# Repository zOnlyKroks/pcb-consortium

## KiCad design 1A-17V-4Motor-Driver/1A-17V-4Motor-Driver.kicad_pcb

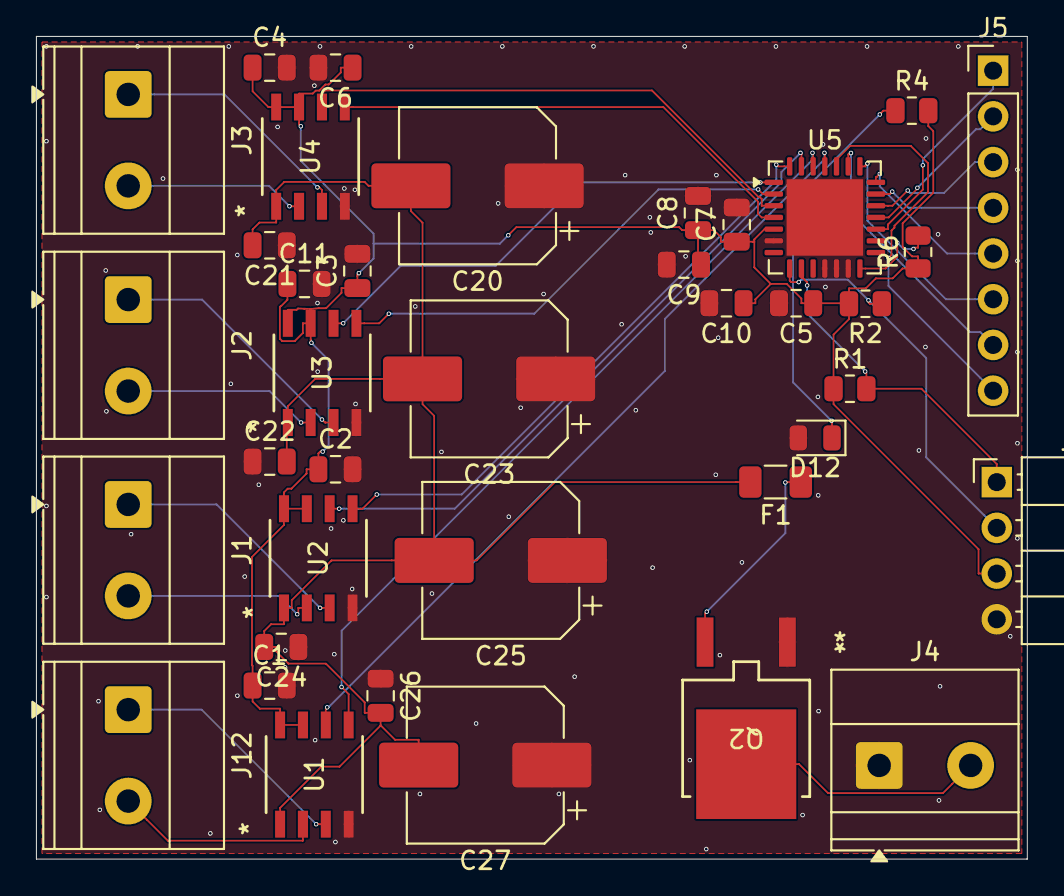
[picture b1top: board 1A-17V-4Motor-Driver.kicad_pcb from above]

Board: 2 copper layers, 55.1 x 45.7 mm, 38 parts (0 on the bottom side), 33 nets.

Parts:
C1, C2, C3, C4, C5, C21, C22, C24, C26: 0.1 uF; C_0805_2012Metric
C6, C7, C8, C9, C10, C11: 22 uF; C_0805_2012Metric
C20, C23, C25, C27: 220 uF; CP_Elec_8x10.5
D12: LED; LED_0805_2012Metric
F1: 4A Fuse; Fuse_1206_3216Metric
J1: OUT2; TerminalBlock_Phoenix_MKDS-1,5-2-5.08_1x02_P5.08mm_Horizont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
J2: OUT3; TerminalBlock_Phoenix_MKDS-1,5-2-5.08_1x02_P5.08mm_Horizont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
J3: OUT4; TerminalBlock_Phoenix_MKDS-1,5-2-5.08_1x02_P5.08mm_Horizont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
J4: 18V; TerminalBlock_Phoenix_MKDS-1,5-2-5.08_1x02_P5.08mm_Horizont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
J5: MUX; PinHeader_1x08_P2.54mm_Vertical
J6: Conn_01x04_Pin; PinHeader_1x04_P2.54mm_Horizontal
J12: OUT1; TerminalBlock_Phoenix_MKDS-1,5-2-5.08_1x02_P5.08mm_Horizont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
Q2: AOD4185; TO252_AOS
R1, R2: 4.7k; R_0805_2012Metric
R4: 330; R_0805_2012Metric
R6: 10k; R_0805_2012Metric
U1, U2, U3, U4: TPM8837C-SO1R; SOP-8_TPK
U5: MCP23017_ML; QFN-28-1EP_6x6mm_P0.65mm_EP4.25x4.25mm

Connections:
+VDC: C20.2, C21.2, C22.2, C23.2, C24.2, C25.2, C26.2, C27.2, F1.2, U1.1 (VM), U2.1 (VM), U3.1 (VM), U4.1 (VM)
/IN1: U1.6 (IN1), U5.25 (GPB0)
/IN2: U1.5 (IN2), U5.26 (GPB1)
/IN3: U2.6 (IN1), U5.27 (GPB2)
/IN4: U2.5 (IN2), U5.28 (GPB3)
/IN5: U3.6 (IN1), U5.1 (GPB4)
/IN6: U3.5 (IN2), U5.2 (GPB5)
/IN7: U4.6 (IN1), U5.3 (GPB6)
/IN8: U4.5 (IN2), U5.4 (GPB7)
/SCK: J6.2, R2.1, U5.8 (SCK)
/SDA: J6.1, R1.2, U5.9 (SDA)
GND: C1.2, C2.2, C3.2, C4.2, C5.2, C6.2, C7.2, C8.2, C9.2, C10.2, C11.2, C20.1, C21.1, C22.1, C23.1, C24.1, C25.1, C26.1, C27.1, D12.2 (A), J4.1, J6.4, Q2.1 (G), U1.4 (GND), U2.4 (GND), U3.4 (GND), U4.4 (GND), U5.6 (VSS), U5.11 (A0), U5.12 (A1), U5.13 (A2), U5.29 (EP)
unnamed: D12.1 (K), R4.1
unnamed: J1.1, U2.3 (OUT2)
unnamed: J1.2, U2.2 (OUT1)
unnamed: J2.1, U3.3 (OUT2)
unnamed: J2.2, U3.2 (OUT1)
unnamed: J3.1, U4.3 (OUT2)
unnamed: J3.2, U4.2 (OUT1)
unnamed: J4.2, Q2.2 (D)
unnamed: J5.1, U5.17 (GPA0)
unnamed: J5.2, U5.18 (GPA1)
unnamed: J5.3, U5.19 (GPA2)
unnamed: J5.4, U5.20 (GPA3)
unnamed: J5.5, U5.21 (GPA4)
unnamed: J5.6, U5.22 (GPA5)
unnamed: J5.7, U5.23 (GPA6)
unnamed: J5.8, U5.24 (GPA7)
unnamed: J12.1, U1.3 (OUT2)
unnamed: J12.2, U1.2 (OUT1)
unnamed: F1.1, Q2.3 (S)
unnamed: R6.2, U5.14 (~RESET)
VCC: C1.1, C2.1, C3.1, C4.1, C5.1, C6.1, C7.1, C8.1, C9.1, C10.1, C11.1, J6.3, R1.1, R2.2, R4.2, R6.1, U1.7 (NSLEEP), U1.8 (VCC), U2.7 (NSLEEP), U2.8 (VCC), U3.7 (NSLEEP), U3.8 (VCC), U4.7 (NSLEEP), U4.8 (VCC), U5.5 (VDD)

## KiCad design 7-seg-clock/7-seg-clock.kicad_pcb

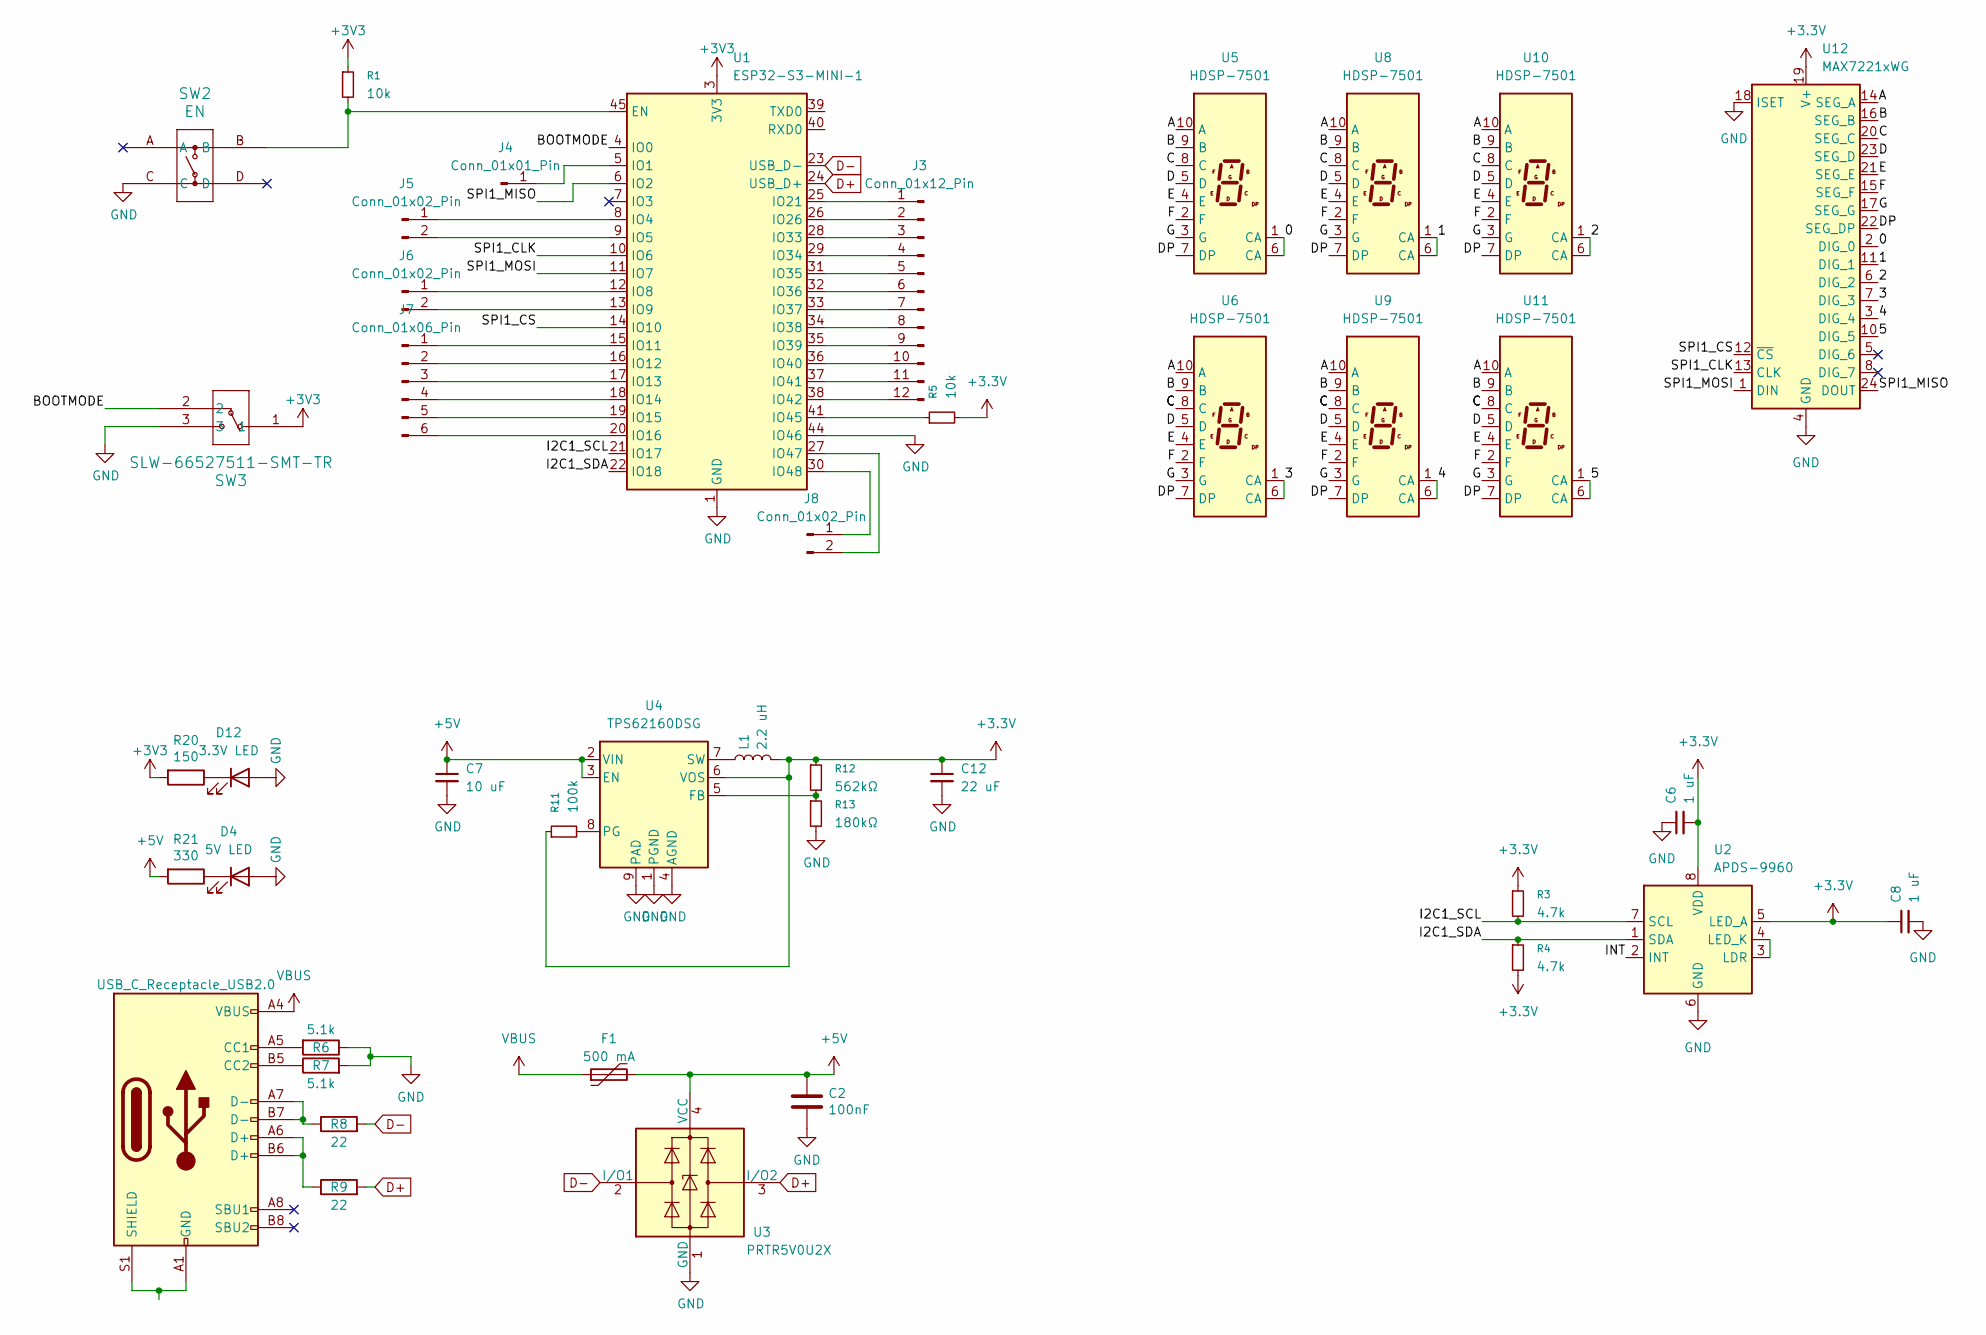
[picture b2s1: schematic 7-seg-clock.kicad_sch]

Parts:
C2: 100nF; C_0805_2012Metric; LCSC C28233
C6, C8: 1 uF; C_1206_3216Metric
C7: 10 uF; C_0805_2012Metric; LCSC Part # C15850
C12: 22 uF; C_0805_2012Metric; LCSC Part # C45783
D4: 5V LED; LED_0805_2012Metric; LCSC Part # C98225
D12: 3.3V LED; LED_0805_2012Metric; LCSC Part # C98225
F1: 500 mA; Fuse_1206_3216Metric; LCSC C135341
J1: USB_C_Receptacle_USB2.0; USB_C_Receptacle_HRO_TYPE-C-31-M-12; JlcRotOffset 180
J3: Conn_01x12_Pin; PinHeader_1x12_P2.54mm_Vertical
J4: Conn_01x01_Pin; PinHeader_1x01_P2.54mm_Vertical
J5, J6, J8: Conn_01x02_Pin; PinHeader_1x02_P2.54mm_Vertical; LCSC Part # C42431798
J7: Conn_01x06_Pin; PinHeader_1x06_P2.54mm_Vertical
L1: 2.2 uH; IND_PA4332.222NLT; LCSC Part # C3222957
R1, R5: 10k; R_0805_2012Metric; LCSC Part # C17414
R3, R4: 4.7k; R_1206_3216Metric
R6, R7: 5.1k; R_0805_2012Metric; LCSC Part # C27834
R8, R9: 22; R_0805_2012Metric; LCSC Part # C17561
R11: 100k; R_0805_2012Metric; LCSC Part # C149504
R12: 562kΩ; R_0805_2012Metric; LCSC Part # C2849274
R13: 180kΩ; R_0805_2012Metric; LCSC Part # C17501
R20: 150; R_0805_2012Metric; LCSC Part # C17471
R21: 330; R_0805_2012Metric; LCSC Part # C17630
SW2: EN; KH-6X6X5H-STM_SKE; LCSC Part # C2837531
SW3: SLW-66527511-SMT-TR; SLW-66527511-SMT-TR_CUD
U1: ESP32-S3-MINI-1; ESP32-S2-MINI-1; LCSC Part # C2913206
U2: APDS-9960; Avago_APDS-9960
U3: PRTR5V0U2X; SOT-143; LCSC C2827688
U4: TPS62160DSG; WSON-8-1EP_2x2mm_P0.5mm_EP0.9x1.6mm_ThermalVias; LCSC Part # C324077
U5, U6, U8, U9, U10, U11: HDSP-7501; HDSP-A151
U12: MAX7221xWG; SOIC-24W_7.5x15.4mm_P1.27mm

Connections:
+3.3V: C6.2, C8.1, C12.1, L1.2, R3.1, R4.2, R5.2, R11.1, R12.1, U2.5 (LED_A), U2.8 (VDD), U4.6 (VOS), U12.19 (V+)
+3V3: R1.1, R20.2, SW3.1, U1.3 (3V3)
+5V: C2.1, C7.1, F1.2, R21.2, U3.4 (VCC), U4.2 (VIN), U4.3 (EN)
/0: U5.1 (CA), U5.6 (CA), U12.2 (DIG_0)
/1: U8.1 (CA), U8.6 (CA), U12.11 (DIG_1)
/2: U10.1 (CA), U10.6 (CA), U12.6 (DIG_2)
/3: U6.1 (CA), U6.6 (CA), U12.7 (DIG_3)
/4: U9.1 (CA), U9.6 (CA), U12.3 (DIG_4)
/5: U11.1 (CA), U11.6 (CA), U12.10 (DIG_5)
/A: U5.10 (A), U6.10 (A), U8.10 (A), U9.10 (A), U10.10 (A), U11.10 (A), U12.14 (SEG_A)
/B: U5.9 (B), U6.9 (B), U8.9 (B), U9.9 (B), U10.9 (B), U11.9 (B), U12.16 (SEG_B)
/BOOTMODE: SW3.2, U1.4 (IO0)
/C: U5.8 (C), U6.8 (C), U8.8 (C), U9.8 (C), U10.8 (C), U11.8 (C), U12.20 (SEG_C)
/D: U5.5 (D), U6.5 (D), U8.5 (D), U9.5 (D), U10.5 (D), U11.5 (D), U12.23 (SEG_D)
/DP: U5.7 (DP), U6.7 (DP), U8.7 (DP), U9.7 (DP), U10.7 (DP), U11.7 (DP), U12.22 (SEG_DP)
/E: U5.4 (E), U6.4 (E), U8.4 (E), U9.4 (E), U10.4 (E), U11.4 (E), U12.21 (SEG_E)
/F: U5.2 (F), U6.2 (F), U8.2 (F), U9.2 (F), U10.2 (F), U11.2 (F), U12.15 (SEG_F)
/G: U5.3 (G), U6.3 (G), U8.3 (G), U9.3 (G), U10.3 (G), U11.3 (G), U12.17 (SEG_G)
/I2C1_SCL: R3.2, U1.21 (IO17), U2.7 (SCL)
/I2C1_SDA: R4.1, U1.22 (IO18), U2.1 (SDA)
/INT: U2.2 (INT)
/SPI1_CLK: U1.10 (IO6), U12.13 (CLK)
/SPI1_CS: U1.14 (IO10), U12.12 (~CS)
/SPI1_MISO: U1.6 (IO2), U12.24 (DOUT)
/SPI1_MOSI: U1.11 (IO7), U12.1 (DIN)
D+: R9.2, U1.24 (USB_D+), U3.3 (I/O2)
D-: R8.2, U1.23 (USB_D-), U3.2 (I/O1)
GND: C2.2, C6.1, C7.2, C8.2, C12.2, D4.2 (A), D12.2 (A), R6.1, R7.2, R13.2, SW2.C, SW3.3, U1.1 (GND), U1.2 (GND), U1.42 (GND), U1.43 (GND), U1.44 (IO46), U1.46 (GND), U1.47 (GND), U1.48 (GND), U1.49 (GND), U1.50 (GND), U1.51 (GND), U1.52 (GND), U1.53 (GND), U1.54 (GND), U1.55 (GND), U1.56 (GND), U1.57 (GND), U1.58 (GND), U1.59 (GND), U1.60 (GND), U1.61 (GND), U1.62 (GND), U1.63 (GND), U1.64 (GND), U1.65 (GND), U2.6 (GND), U3.1 (GND), U4.1 (PGND), U4.4 (AGND), U4.9 (PAD), U12.4 (GND), U12.9 (GND), U12.18 (ISET)
unnamed: D4.1 (K), R21.1
unnamed: D12.1 (K), R20.1
unnamed: J1.A5 (CC1), R6.2
unnamed: J1.B5 (CC2), R7.1
unnamed: J1.A6 (D+), J1.B6 (D+), R9.1
unnamed: J1.A7 (D-), J1.B7 (D-), R8.1
unnamed: J1.A1 (GND), J1.A12 (GND), J1.B1 (GND), J1.B12 (GND), J1.S1 (SHIELD)
unnamed: J3.1, U1.25 (IO21)
unnamed: J3.2, U1.26 (IO26)
unnamed: J3.3, U1.28 (IO33)
unnamed: J3.4, U1.29 (IO34)
unnamed: J3.5, U1.31 (IO35)
unnamed: J3.6, U1.32 (IO36)
unnamed: J3.7, U1.33 (IO37)
unnamed: J3.8, U1.34 (IO38)
unnamed: J3.9, U1.35 (IO39)
unnamed: J3.10, U1.36 (IO40)
unnamed: J3.11, U1.37 (IO41)
unnamed: J3.12, U1.38 (IO42)
unnamed: J4.1, U1.5 (IO1)
unnamed: J5.1, U1.8 (IO4)
unnamed: J5.2, U1.9 (IO5)
unnamed: J6.1, U1.12 (IO8)
unnamed: J6.2, U1.13 (IO9)
unnamed: J7.1, U1.15 (IO11)
unnamed: J7.2, U1.16 (IO12)
unnamed: J7.3, U1.17 (IO13)
unnamed: J7.4, U1.18 (IO14)
unnamed: J7.5, U1.19 (IO15)
unnamed: J7.6, U1.20 (IO16)
unnamed: J8.1, U1.30 (IO48)
unnamed: J8.2, U1.27 (IO47)
unnamed: R1.2, SW2.B, U1.45 (EN)
unnamed: R5.1, U1.41 (IO45)
unnamed: U2.3 (LDR), U2.4 (LED_K)
unnamed: R12.2, R13.1, U4.5 (FB)
unnamed: R11.2, U4.8 (PG)
unnamed: L1.1, U4.7 (SW)
VBUS: F1.1, J1.A4 (VBUS), J1.A9 (VBUS), J1.B4 (VBUS), J1.B9 (VBUS)

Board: 6 copper layers, 42 parts (0 on the bottom side), 66 nets, no tracks yet.

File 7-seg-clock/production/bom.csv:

Designator,Footprint,Quantity,Value,LCSC Part #
C12,0805,1,22 uF,C45783
C2,0805,1,100nF,C28233
"C6, C8",1206,2,1 uF,
C7,0805,1,10 uF,C15850
D12,0805,1,3.3V LED,C98225
D4,0805,1,5V LED,C98225
F1,1206,1,500 mA,C135341
J1,USB_C_Receptacle_HRO_TYPE-C-31-M-12,1,USB_C_Receptacle_USB2.0,C165948
J3,PinHeader_1x12_P2.54mm_Vertical,1,Conn_01x12_Pin,
J4,PinHeader_1x01_P2.54mm_Vertical,1,Conn_01x01_Pin,
"J5, J6, J8",PinHeader_1x02_P2.54mm_Vertical,3,Conn_01x02_Pin,C42431798
J7,PinHeader_1x06_P2.54mm_Vertical,1,Conn_01x06_Pin,
L1,IND_PA4332.222NLT,1,2.2 uH,C3222957
"R1, R5",0805,2,10k,C17414
R11,0805,1,100k,C149504
R12,0805,1,562kΩ,C2849274
R13,0805,1,180kΩ,C17501
R20,0805,1,150,C17471
R21,0805,1,330,C17630
"R3, R4",1206,2,4.7k,
"R6, R7",0805,2,5.1k,C27834
"R8, R9",0805,2,22,C17561
SW2,KH-6X6X5H-STM_SKE,1,EN,C2837531 
SW3,SLW-66527511-SMT-TR_CUD,1,SLW-66527511-SMT-TR,
U1,ESP32-S2-MINI-1,1,ESP32-S3-MINI-1,C2913206 
"U10, U11, U5, U6, U8, U9",HDSP-A151,6,HDSP-7501,
U12,SOIC-24W_7.5x15.4mm_P1.27mm,1,MAX7221xWG,
U2,Avago_APDS-9960,1,APDS-9960,
U3,SOT-143,1,PRTR5V0U2X,C2827688
U4,WSON-8-1EP_2x2mm_P0.5mm_EP0.9x1.6mm_ThermalVias,1,TPS62160DSG,C324077

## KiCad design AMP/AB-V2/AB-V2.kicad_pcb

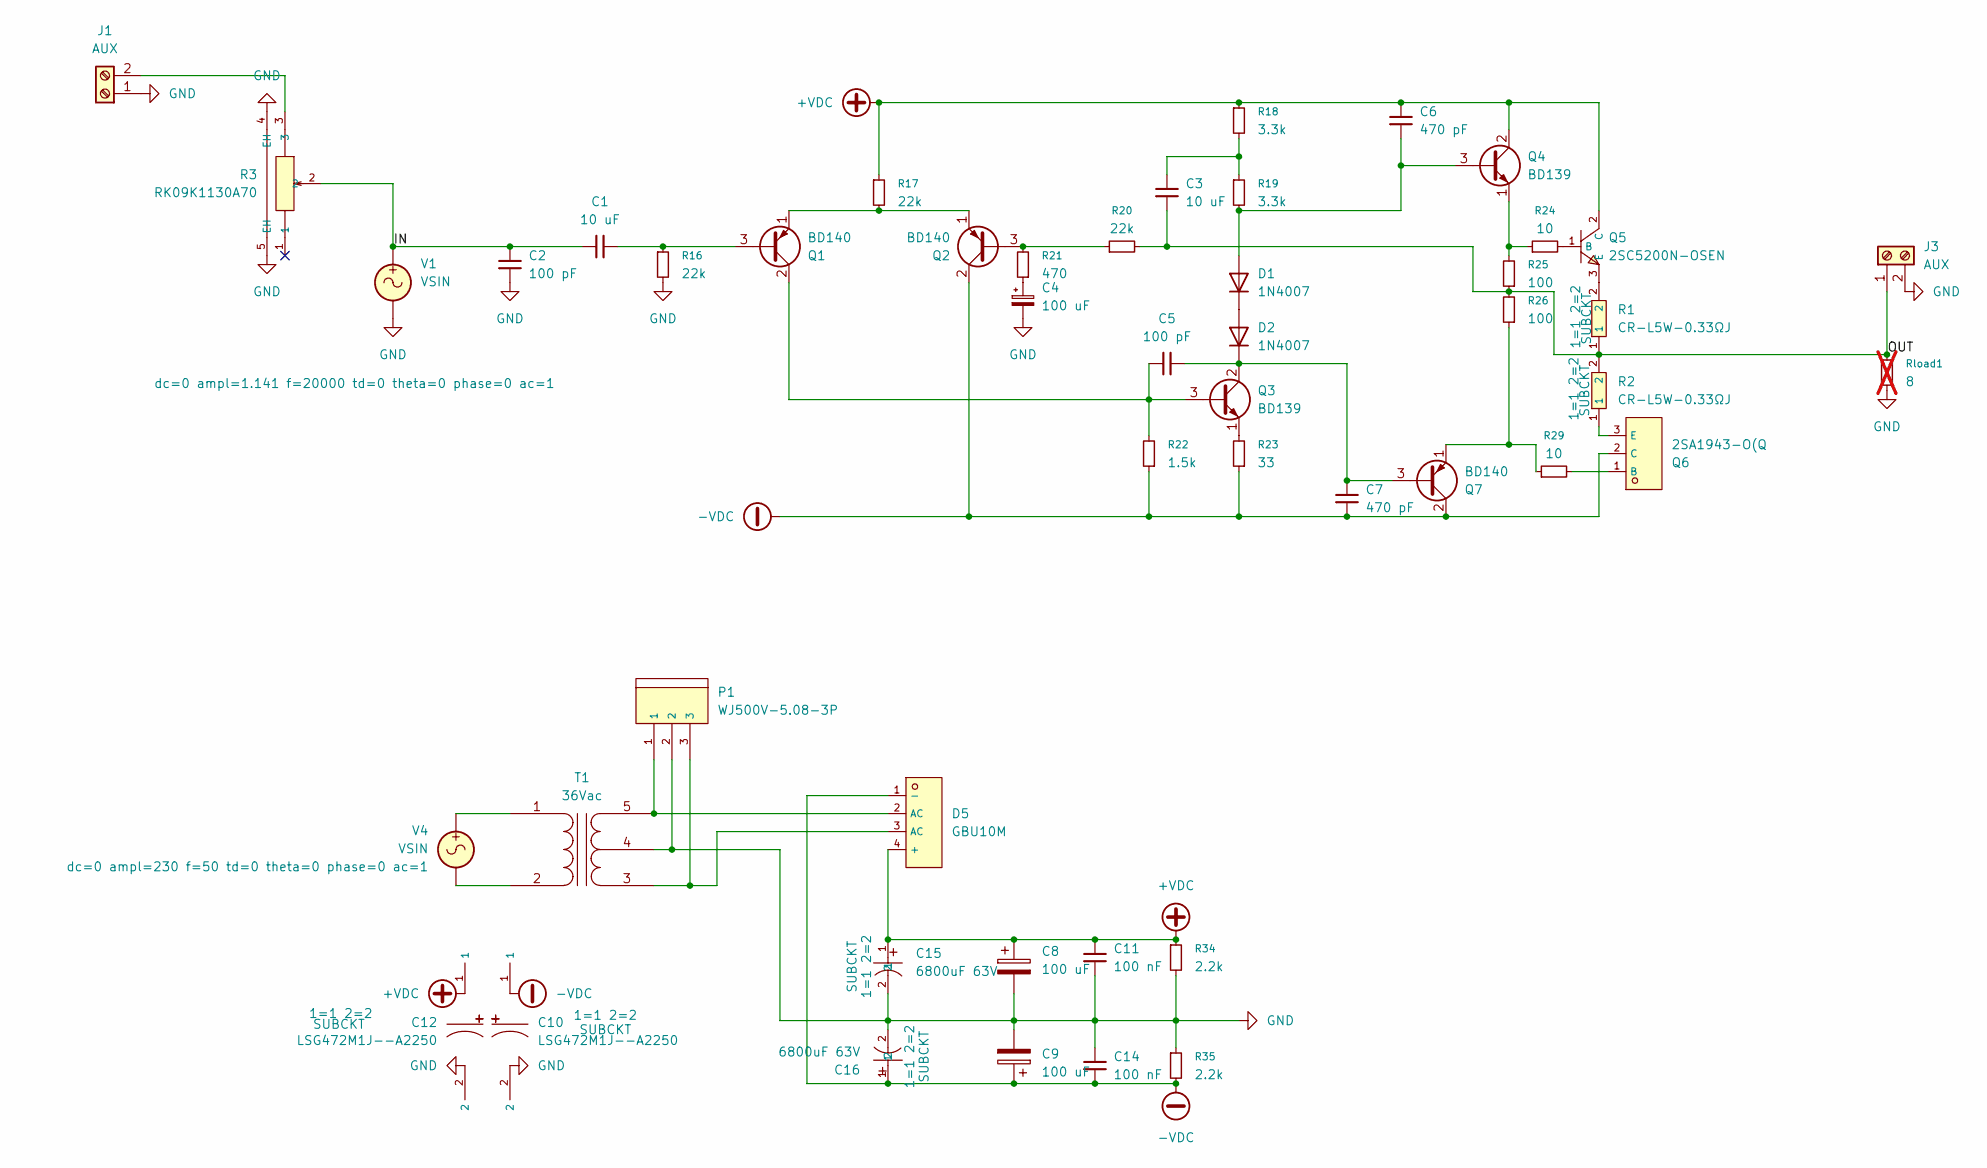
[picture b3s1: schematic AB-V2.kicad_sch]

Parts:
C1, C3: 10 uF; C_1206_3216Metric
C2, C5: 100 pF; C_1206_3216Metric
C4: 100 uF; C_Elec_6.3x7.7
C6, C7: 470 pF; C_1206_3216Metric
C8, C9: 100 uF; CP_Radial_D8.0mm_P3.50mm
C10, C12: LSG472M1J--A2250; C316462_CAP-TH_BD22_0-P10_00-D2_3-FD; LCSC C316462
C11, C14: 100 nF; C_0805_2012Metric
C15, C16: 6800uF 63V; C46441_CAP-TH_BD25_0-P10_00-D2_3-FD; LCSC C46441
D1, D2: 1N4007; D_DO-41_SOD81_P10.16mm_Horizontal
D5: GBU10M; C970322_GBU_4P-L22_0-W3_5-P5_08; LCSC C970322
J1, J3: AUX; WJ500V-5.08-2P
P1: WJ500V-5.08-3P; C72334_CONN-TH_3P-P5_00_WJ500V-5_08-3P; LCSC C72334
Q1, Q2, Q7: BD140; TO-126-3_Vertical
Q3, Q4: BD139; TO-126-3_Vertical
Q5: 2SC5200N-OSEN; C49055716_TO-3P-3_L15_6-W4_8-P5_45-L; LCSC C49055716
Q6: 2SA1943-O(Q; C545244_TO-3PL_L20_0-W5_0-P5_45-L_1; LCSC C545244
R1, R2: CR-L5W-0.33ΩJ; C334290_RES-TH_BD9_5-L22_0-P26_00-D0_7; LCSC C334290
R3: RK09K1130A70; C351173_RES-TH_RK09K1130A70; LCSC C351173
R16, R17, R20: 22k; R_0805_2012Metric
R18, R19: 3.3k; R_0805_2012Metric
R21: 470; R_0805_2012Metric
R22: 1.5k; R_0805_2012Metric
R23: 33; R_0805_2012Metric
R24, R29: 10; R_0805_2012Metric
R25, R26: 100; R_1206_3216Metric
R34, R35: 2.2k; R_0805_2012Metric
Rload1: 8; not fitted
T1: 36Vac
V1, V4: VSIN; TQFP-44_10x10mm_P0.8mm

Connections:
+VDC: C6.2, C8.1, C11.2, C12.1, C15.1, D5.4 (+), Q4.2 (C), Q5.2 (C), R17.1, R18.1, R34.1
-VDC: C7.1, C9.1, C10.1, C14.1, C16.1, D5.1 (-), Q2.2 (C), Q6.2 (C), Q7.2 (C), R22.1, R23.1, R35.2
/IN: C1.1, C2.2, R3.2, V1.1
/OUT: C3.1, J3.1, R1.1, R2.2, R20.2, R25.1, R26.2, Rload1.2
GND: C2.1, C4.2, C8.2, C9.2, C10.2, C11.1, C12.2, C14.2, C15.2, C16.2, J1.1, J3.2, P1.2, R3.4 (EH), R3.5 (EH), R16.2, R34.2, R35.1, Rload1.1, T1.4 (SC), V1.2
unnamed: C3.2, R18.2, R19.1
unnamed: C4.1, R21.1
unnamed: C6.1, D1.2 (A), Q4.3 (B), R19.2
unnamed: D1.1 (K), D2.2 (A)
unnamed: C5.1, C7.2, D2.1 (K), Q3.2 (C), Q7.3 (B)
unnamed: D5.2 (AC), P1.1, T1.5 (SB)
unnamed: D5.3 (AC), P1.3, T1.3 (SA)
unnamed: J1.2, R3.3
unnamed: C1.2, Q1.3 (B), R16.1
unnamed: C5.2, Q1.2 (C), Q3.3 (B), R22.2
unnamed: Q1.1 (E), Q2.1 (E), R17.2
unnamed: Q2.3 (B), R20.1, R21.2
unnamed: Q3.1 (E), R23.2
unnamed: Q4.1 (E), R24.1, R25.2
unnamed: Q5.1 (B), R24.2
unnamed: Q5.3 (E), R1.2
unnamed: Q6.1 (B), R29.2
unnamed: Q6.3 (E), R2.1
unnamed: Q7.1 (E), R26.1, R29.1
unnamed: T1.1 (AA), V4.1
unnamed: T1.2 (AB), V4.2

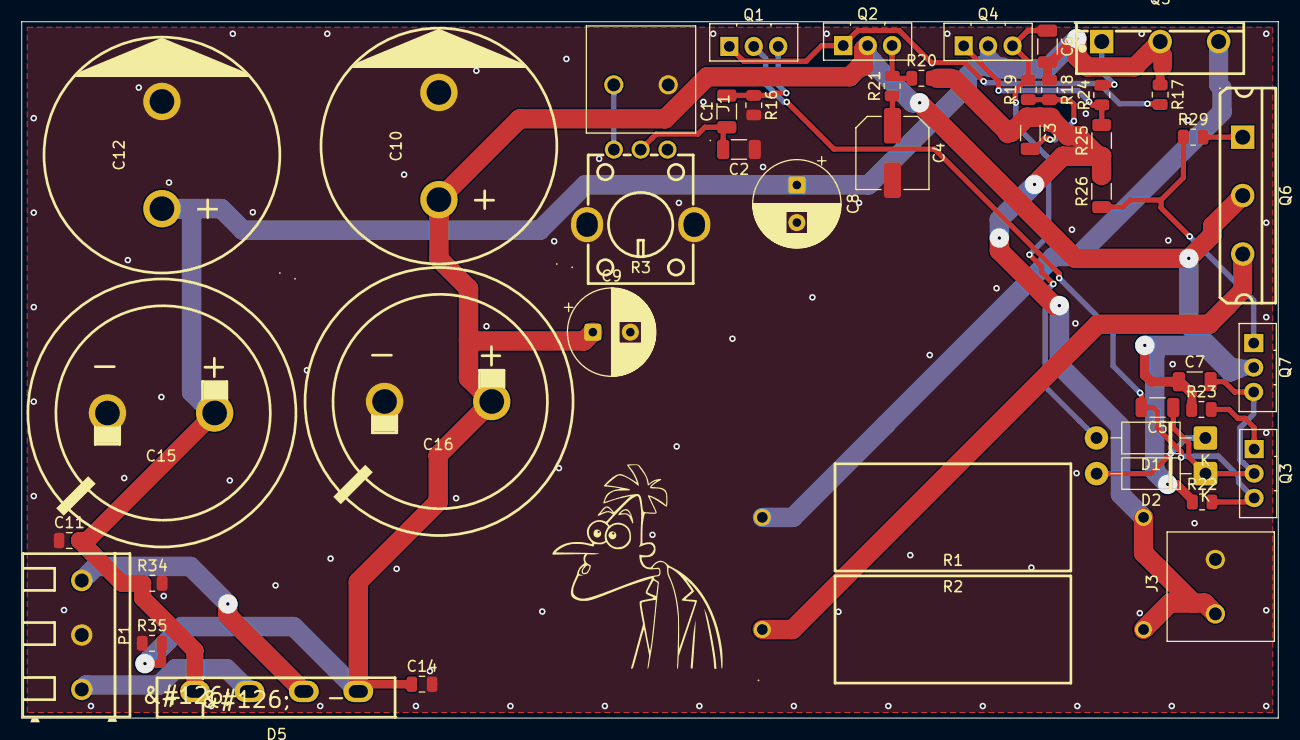
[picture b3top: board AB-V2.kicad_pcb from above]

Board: 2 copper layers, 117.2 x 65.0 mm, 45 parts (0 on the bottom side), 24 nets.

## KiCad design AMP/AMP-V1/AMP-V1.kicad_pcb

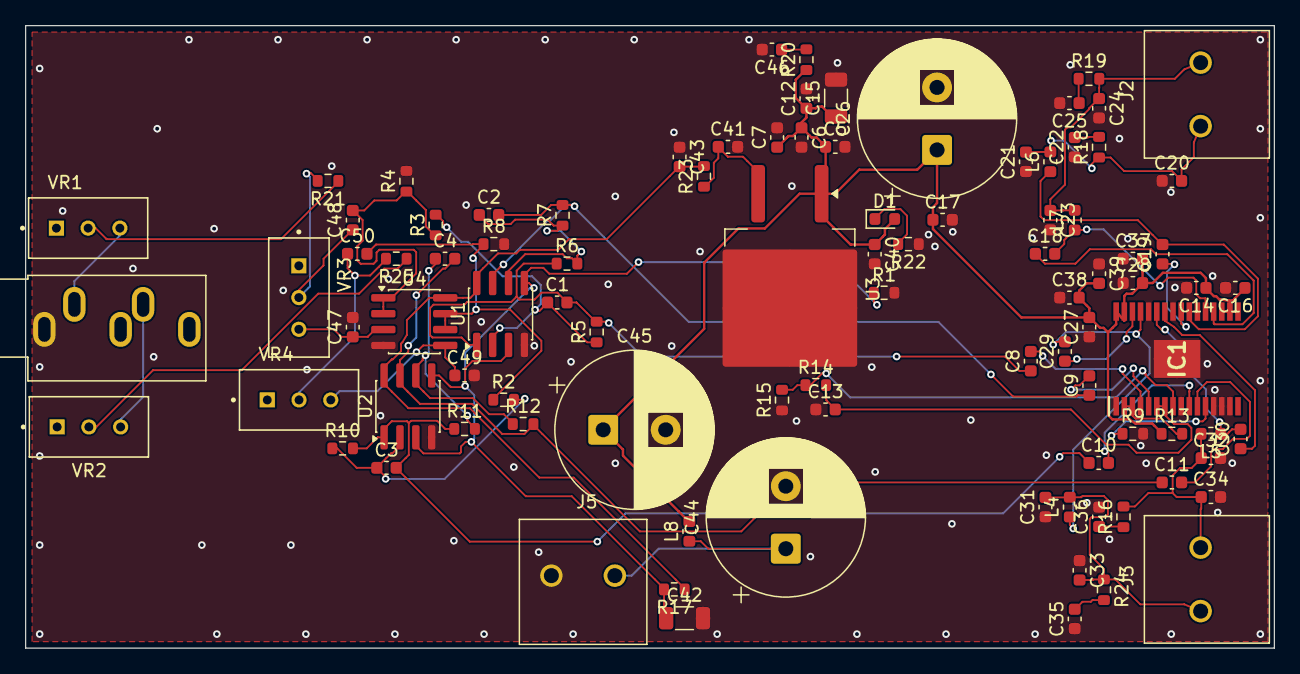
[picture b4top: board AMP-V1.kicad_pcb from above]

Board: 2 copper layers, 99.9 x 49.8 mm, 94 parts (0 on the bottom side), 50 nets.

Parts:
C1, C2, C3, C4: 22 pF; C_0603_1608Metric
C5, C8, C9, C10, C11, C16, C27, C28, C38, C40, C41: 10uF; C_0603_1608Metric
C6, C7, C12, C17, C39, C46: 100nF; C_0603_1608Metric
C13: 2.2 uF; C_0603_1608Metric
C14, C37, C43: 220 uF; C_0603_1608Metric
C15, C42: 47uF; C_1206_3216Metric
C18, C19, C29, C30: 0.22 uF; C_0603_1608Metric
C20, C23, C31, C32: 680 nF; C_0603_1608Metric
C21, C24, C33, C34: 1 nF; C_0603_1608Metric
C22, C25, C35, C36, C47, C48, C49, C50: 10 nF; C_0603_1608Metric
C26, C44, C45: 470 uF; CP_Radial_D12.5mm_P5.00mm
D1: LED; LED_0603_1608Metric
IC1: TPA3116D2DAD; SOP65P810X120-33N
J2: L; WJ500V-5.08-2P
J3, J5: R; WJ500V-5.08-2P
J4: AudioJack3_SwitchTR; Jack_3.5mm_CUI_SJ1-3535NG_Horizontal
L4, L5, L6, L7, L8: 10 uH; L_0603_1608Metric
R1, R2, R3, R5, R6, R7, R10, R11, R12, R17, R21, R22, R25: 10K; R_0603_1608Metric
R4, R8, R9, R13: 100K; R_0603_1608Metric
R14: 75k Ohm; R_0603_1608Metric
R15: 47k Ohm; R_0603_1608Metric
R16, R18, R19, R20, R24: 3.3 Ohm; R_0603_1608Metric
R23: 2.2 Ohm; R_0603_1608Metric
U1, U2, U4: NE5532; SOIC-8_3.9x4.9mm_P1.27mm
U3: LM7812_TO220; TO-263-2
VR1, VR2, VR3, VR4: 3296W-1-103LF; TRIM_3296W-1-103LF

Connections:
+12V: C43.2, R17.1, R23.2, U1.8 (V+), U2.8 (V+), U4.8 (V+)
/GAIN: IC1.8 (GAIN/SLV), R14.1, R15.2
/GVDD: C13.2, IC1.6 (PLIMIT), IC1.7 (GVDD), R14.2
/LIN-N: C4.2, C11.1, R12.2, U2.7
/LIN-P: C3.2, C10.1, R10.2, R11.1, U2.1
/LR-Decode/MID-REF: C42.1, R1.1, R17.2, U1.3 (+), U1.5 (+), U2.3 (+), U2.5 (+)
/RIN-N: C2.2, C9.1, R7.2, U1.7
/RIN-P: C1.2, C8.1, R5.2, R6.1, U1.1
/RING-RIGHT: R25.1, VR2.2
/TIP-LEFT: R21.1, VR1.2
GND: C5.2, C6.2, C7.2, C12.2, C13.1, C14.2, C15.2, C16.2, C17.2, C20.1, C21.1, C22.1, C23.2, C24.2, C25.2, C26.2, C27.1, C28.1, C31.1, C32.2, C33.1, C34.2, C35.1, C36.2, C37.1, C38.1, C39.1, C40.2, C41.2, C42.2, C43.1, C44.2, C45.2, C46.2, C47.2, C49.2, IC1.1 (MODSEL), IC1.9 (GND_1), IC1.13 (AM2), IC1.14 (AM1), IC1.15 (AM0), IC1.25 (GND_3), IC1.28 (GND_4), IC1.33 (GND_5), J4.S, J5.1, R1.2, R4.2, R8.2, R9.2, R15.1, R22.1, U1.4 (V-), U2.4 (V-), U3.2 (GND), U4.4 (V-)
unnamed: C22.2, R18.2
unnamed: C25.1, R19.1
unnamed: C35.2, R24.2
unnamed: C36.1, R16.1
unnamed: C46.1, R20.2
unnamed: C48.1, R21.2, VR3.2
unnamed: C50.1, R25.2, VR4.2
unnamed: D1.1 (K), R22.2
unnamed: C18.1, IC1.20 (BSNL)
unnamed: C30.1, IC1.26 (BSNR)
unnamed: C19.1, IC1.24 (BSPL)
unnamed: C29.1, IC1.30 (BSPR)
unnamed: IC1.2 (SD), IC1.3 (FAULT), R13.2
unnamed: C11.2, IC1.11 (LINN)
unnamed: C10.2, IC1.10 (LINP)
unnamed: IC1.12 (MUTE), R9.1
unnamed: C18.2, IC1.21 (OUTNL), L7.1
unnamed: C30.2, IC1.27 (OUTNR), L5.1
unnamed: C19.2, IC1.23 (OUTPL), L6.1
unnamed: C29.2, IC1.29 (OUTPR), L4.1
unnamed: C9.2, IC1.5 (RINN)
unnamed: C8.2, IC1.4 (RINP)
unnamed: C20.2, C21.2, J2.1, L6.2, R18.1
unnamed: C23.1, C24.1, J2.2, L7.2, R19.2
unnamed: C31.2, C33.2, J3.1, L4.2, R24.1
unnamed: C32.1, C34.1, J3.2, L5.2, R16.2
unnamed: J4.R, VR2.3
unnamed: J4.T, VR1.3
unnamed: C44.1, J5.2, L8.1
unnamed: C1.1, R3.2, R5.1, U1.2 (-)
unnamed: C2.1, R6.2, R7.1, U1.6 (-)
unnamed: C3.1, R2.2, R10.1, U2.2 (-)
unnamed: C4.1, R11.2, R12.1, U2.6 (-)
unnamed: C41.1, R23.1, U3.3 (VO)
unnamed: C47.1, U4.3 (+), VR3.3
unnamed: C48.2, R3.1, R4.1, U4.1, U4.2 (-)
unnamed: C49.1, U4.5 (+), VR4.3
unnamed: C50.2, R2.1, R8.1, U4.6 (-), U4.7
PVCC: C5.1, C6.1, C7.1, C12.1, C14.1, C15.1, C16.1, C17.1, C26.1, C27.2, C28.2, C37.2, C38.2, C39.2, C40.1, C45.1, D1.2 (A), IC1.17 (AVCC), IC1.18 (PVCC_1), IC1.19 (PVCC_2), IC1.31 (PVCC_3), IC1.32 (PVCC_4), L8.2, R13.1, R20.1, U3.1 (VI)

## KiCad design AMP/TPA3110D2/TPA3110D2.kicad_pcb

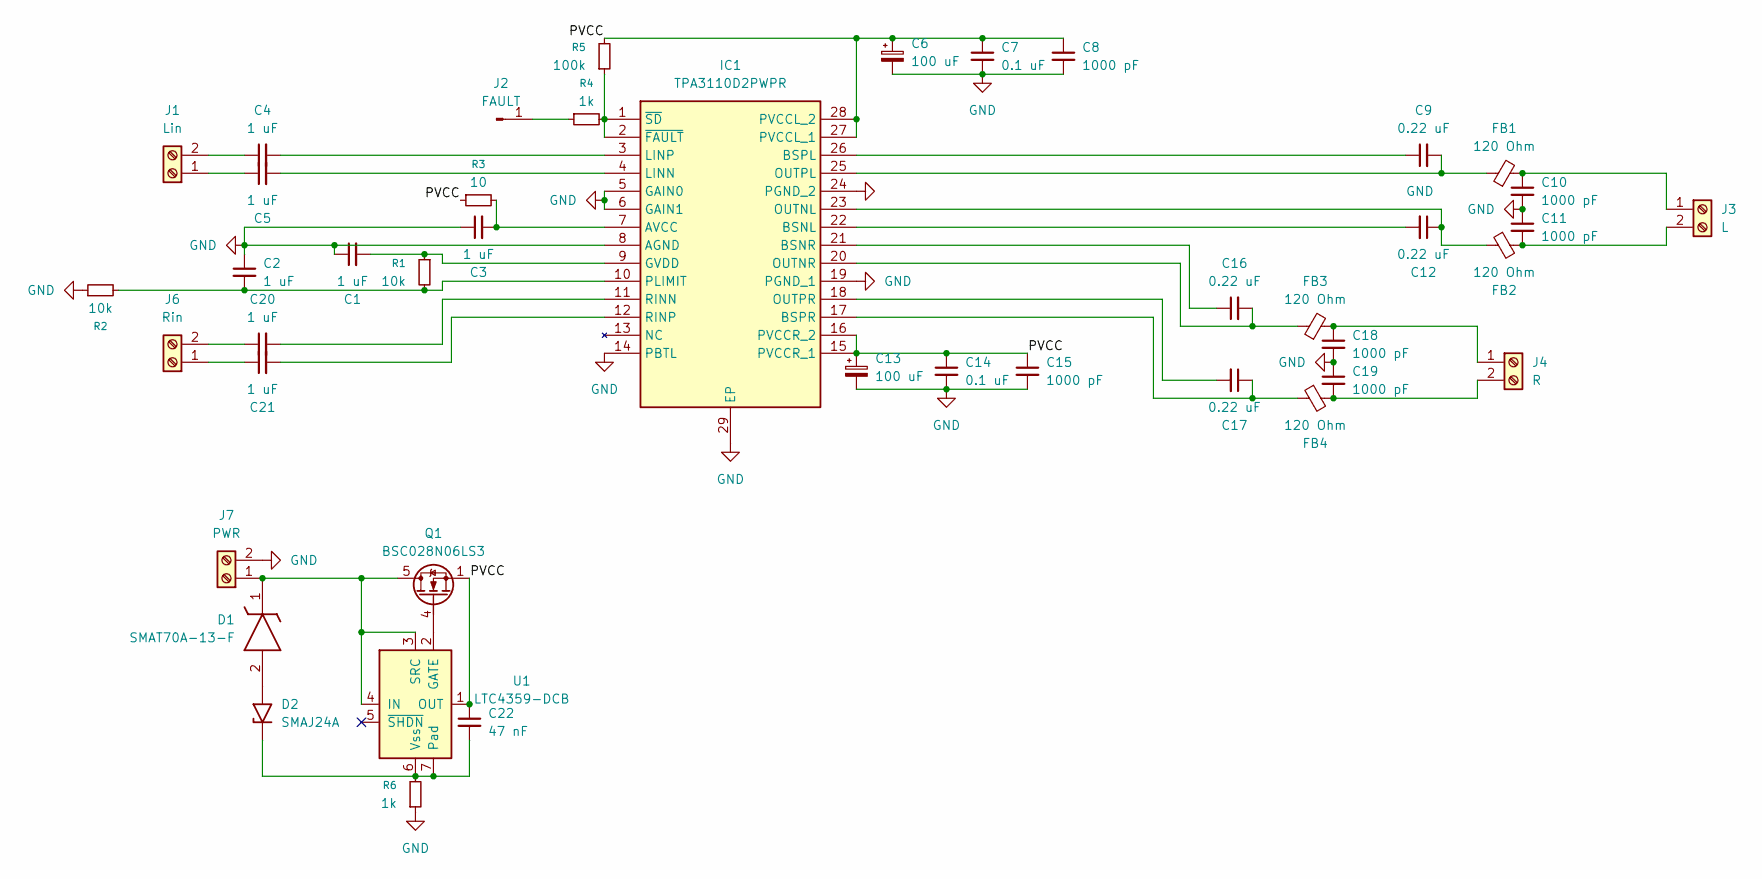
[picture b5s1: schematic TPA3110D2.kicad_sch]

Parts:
C1, C2, C3, C4, C5, C20, C21: 1 uF; C_0603_1608Metric
C6, C13: 100 uF; CP_Elec_6.3x7.7
C7, C14: 0.1 uF; C_0603_1608Metric
C8, C10, C11, C15, C18, C19: 1000 pF; C_0603_1608Metric
C9, C12, C16, C17: 0.22 uF; C_0603_1608Metric
C22: 47 nF; C_0603_1608Metric
D1: SMAT70A-13-F; DIOM5226X230N; Mouser Part Number 621-SMAT70A-13-F
D2: SMAJ24A; D_SMA
FB1, FB2, FB3, FB4: 120 Ohm; R_0603_1608Metric
IC1: TPA3110D2PWPR; SOP65P640X120-29N; Mouser Part Number 595-TPA3110D2PWPR
J1: Lin; WJ500V-5.08-2P
J2: FAULT; PinHeader_1x01_P2.54mm_Vertical
J3: L; WJ500V-5.08-2P
J4: R; WJ500V-5.08-2P
J6: Rin; WJ500V-5.08-2P
J7: PWR; WJ500V-5.08-2P
Q1: BSC028N06LS3; TDSON-8-1
R1, R2: 10k; R_0603_1608Metric
R3: 10; R_0603_1608Metric
R4, R6: 1k; R_0603_1608Metric
R5: 100k; R_0603_1608Metric
U1: LTC4359-DCB; DFN-6-1EP_3x2mm_P0.5mm_EP1.65x1.35mm

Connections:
/PVCC: C6.1, C7.1, C8.1, C13.1, C14.1, C15.1, C22.1, IC1.15 (PVCCR_1), IC1.16 (PVCCR_2), IC1.27 (PVCCL_1), IC1.28 (PVCCL_2), Q1.1 (S), Q1.2 (S), Q1.3 (S), R3.1, R5.2, U1.1 (OUT)
GND: C1.1, C2.1, C3.1, C6.2, C7.2, C8.2, C10.2, C11.1, C13.2, C14.2, C15.2, C18.2, C19.1, IC1.5 (GAIN0), IC1.6 (GAIN1), IC1.8 (AGND), IC1.14 (PBTL), IC1.19 (PGND_1), IC1.24 (PGND_2), IC1.29 (EP), J7.2, R2.1, R6.1
unnamed: D1.2 (A), D2.2 (A2)
unnamed: D1.1 (K), J7.1, Q1.5 (D), U1.3 (SRC), U1.4 (IN)
unnamed: C22.2, D2.1 (A1), R6.2, U1.6 (Vss), U1.7 (Pad)
unnamed: C3.2, IC1.7 (AVCC), R3.2
unnamed: C12.2, IC1.22 (BSNL)
unnamed: C16.1, IC1.21 (BSNR)
unnamed: C9.1, IC1.26 (BSPL)
unnamed: C17.1, FB4.1, IC1.17 (BSPR)
unnamed: C1.2, IC1.9 (GVDD), R1.1
unnamed: C5.2, IC1.4 (LINN)
unnamed: C4.2, IC1.3 (LINP)
unnamed: C12.1, FB2.1, IC1.23 (OUTNL)
unnamed: C16.2, FB3.1, IC1.20 (OUTNR)
unnamed: C9.2, FB1.1, IC1.25 (OUTPL)
unnamed: C17.2, IC1.18 (OUTPR)
unnamed: C2.2, IC1.10 (PLIMIT), R1.2, R2.2
unnamed: C20.2, IC1.11 (RINN)
unnamed: C21.2, IC1.12 (RINP)
unnamed: IC1.1 (~SD), IC1.2 (~FAULT), R4.2, R5.1
unnamed: C5.1, J1.1
unnamed: C4.1, J1.2
unnamed: J2.1 (Pin_1_1), R4.1
unnamed: C10.1, FB1.2, J3.1
unnamed: C11.2, FB2.2, J3.2
unnamed: C18.1, FB3.2, J4.1
unnamed: C19.2, FB4.2, J4.2
unnamed: C21.1, J6.1
unnamed: C20.1, J6.2
unnamed: Q1.4 (G), U1.2 (GATE)

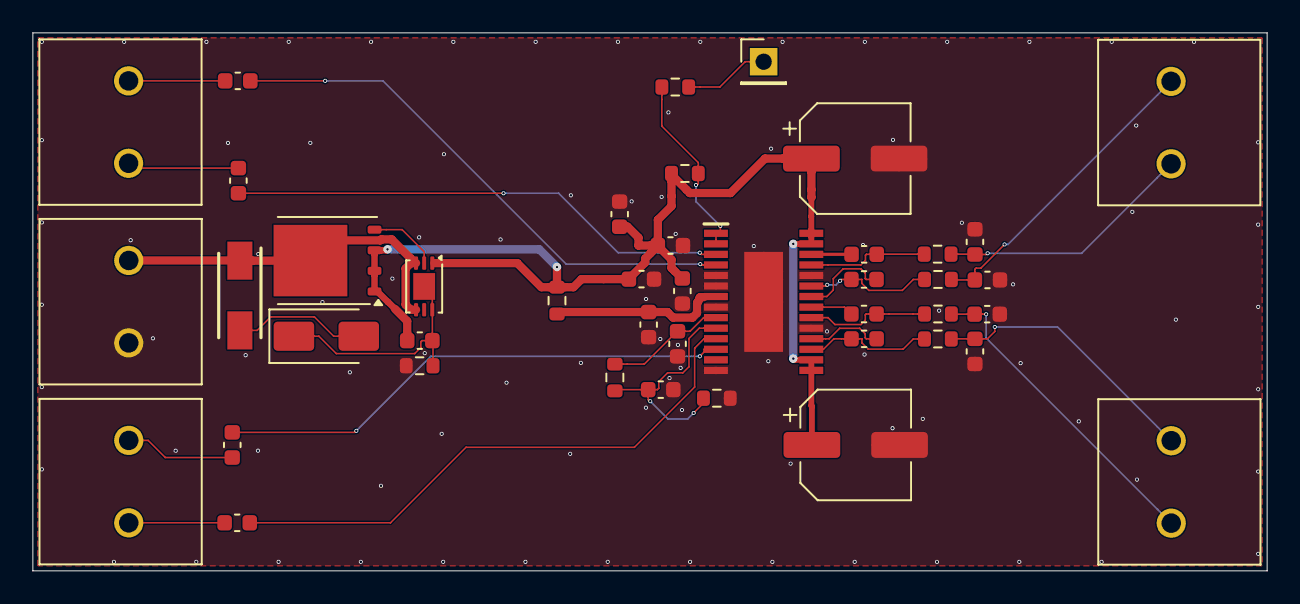
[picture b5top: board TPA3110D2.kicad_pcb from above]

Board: 2 copper layers, 76.1 x 33.2 mm, 43 parts (0 on the bottom side), 31 nets.

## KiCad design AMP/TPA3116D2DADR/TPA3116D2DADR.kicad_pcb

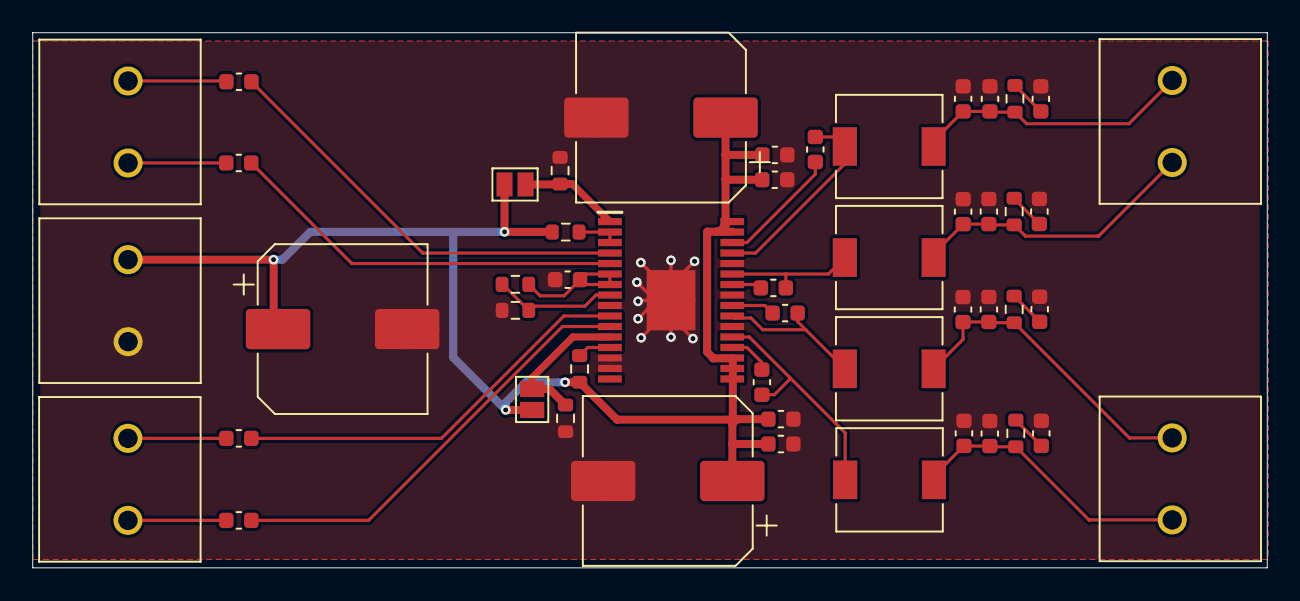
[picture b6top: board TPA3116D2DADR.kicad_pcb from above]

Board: 2 copper layers, 76.5 x 33.2 mm, 50 parts (0 on the bottom side), 32 nets.

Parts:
C1, C2, C3, C4, C5, C9, C12: 1 uF; C_0603_1608Metric
C8, C11, C14, C15, C16, C17: 100 nF; C_0603_1608Metric
C10, C13, C30: 220 uF; CP_Elec_10x10
C18, C19, C24, C25: 680 nF; C_0603_1608Metric
C20, C21, C26, C27: 1 nF; C_0603_1608Metric
C22, C23, C28, C29: 10 nF; C_0603_1608Metric
IC1: TPA3116D2DADR; SOP65P810X120-33N
J1: Rin; WJ500V-5.08-2P
J2: Lin; WJ500V-5.08-2P
J3: Rout; WJ500V-5.08-2P
J4: Lout; WJ500V-5.08-2P
J7: PWR; WJ500V-5.08-2P
JP1: mode_sel; SolderJumper-2_P1.3mm_Open_Pad1.0x1.5mm
JP2: mute; SolderJumper-2_P1.3mm_Open_Pad1.0x1.5mm
L1, L2, L3, L4: 10 uH; L_6.3x6.3_H3
R1, R4, R5: 100k; R_0603_1608Metric
R3: 20k; R_0603_1608Metric
R6, R12: 10k; R_0603_1608Metric
R7, R8, R9, R10: 3.3; R_0603_1608Metric

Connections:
/GVDD: C5.2, IC1.6 (PLIMIT), IC1.7 (GVDD), R4.2
GND: C5.1, C8.1, C9.1, C10.2, C11.2, C12.2, C13.2, C18.2, C19.1, C20.1, C21.2, C22.2, C23.2, C24.1, C25.2, C26.2, C27.1, C28.2, C29.2, C30.2, IC1.9 (GND_1), IC1.14 (AM1), IC1.15 (AM0), IC1.22 (GND_2), IC1.25 (GND_3), IC1.28 (GND_4), IC1.33 (EP), J7.2, R3.1, R6.2, R12.2
unnamed: C22.1, R7.2
unnamed: C23.1, R8.1
unnamed: C28.1, R9.2
unnamed: C29.1, R10.1
unnamed: IC1.13 (AM2), R1.2
unnamed: C17.2, IC1.20 (BSNL)
unnamed: C15.2, IC1.26 (BSNR)
unnamed: C16.2, IC1.24 (BSPL)
unnamed: C14.2, IC1.30 (BSPR)
unnamed: IC1.2 (SDZ), IC1.3 (FAULTZ), R5.1
unnamed: IC1.8 (GAIN/SLV), R3.2, R4.1
unnamed: C4.2, IC1.11 (LINN)
unnamed: C3.2, IC1.10 (LINP)
unnamed: IC1.1 (MODSEL), JP1.2 (B), R6.1
unnamed: IC1.12 (MUTE), JP2.2 (B), R12.1
unnamed: C17.1, IC1.21 (OUTNL), L4.1
unnamed: C15.1, IC1.27 (OUTNR), L2.1
unnamed: C16.1, IC1.23 (OUTPL), L3.1
unnamed: C14.1, IC1.29 (OUTPR), L1.1
unnamed: C2.2, IC1.5 (RINN)
unnamed: C1.2, IC1.4 (RINP)
unnamed: C1.1, J1.1
unnamed: C2.1, J1.2
unnamed: C3.1, J2.1
unnamed: C4.1, J2.2
unnamed: C18.1, C20.2, J3.1, L2.2, R8.2
unnamed: C19.2, C21.1, J3.2, L1.2, R7.1
unnamed: C25.1, C27.2, J4.1, L4.2, R10.2
unnamed: C24.2, C26.1, J4.2, L3.2, R9.1
VCC: C8.2, C9.2, C10.1, C11.1, C12.1, C13.1, C30.1, IC1.17 (AVCC), IC1.18 (PVCC_1), IC1.19 (PVCC_2), IC1.31 (PVCC_3), IC1.32 (PVCC_4), J7.1, JP1.1 (A), JP2.1 (A), R1.1, R5.2
